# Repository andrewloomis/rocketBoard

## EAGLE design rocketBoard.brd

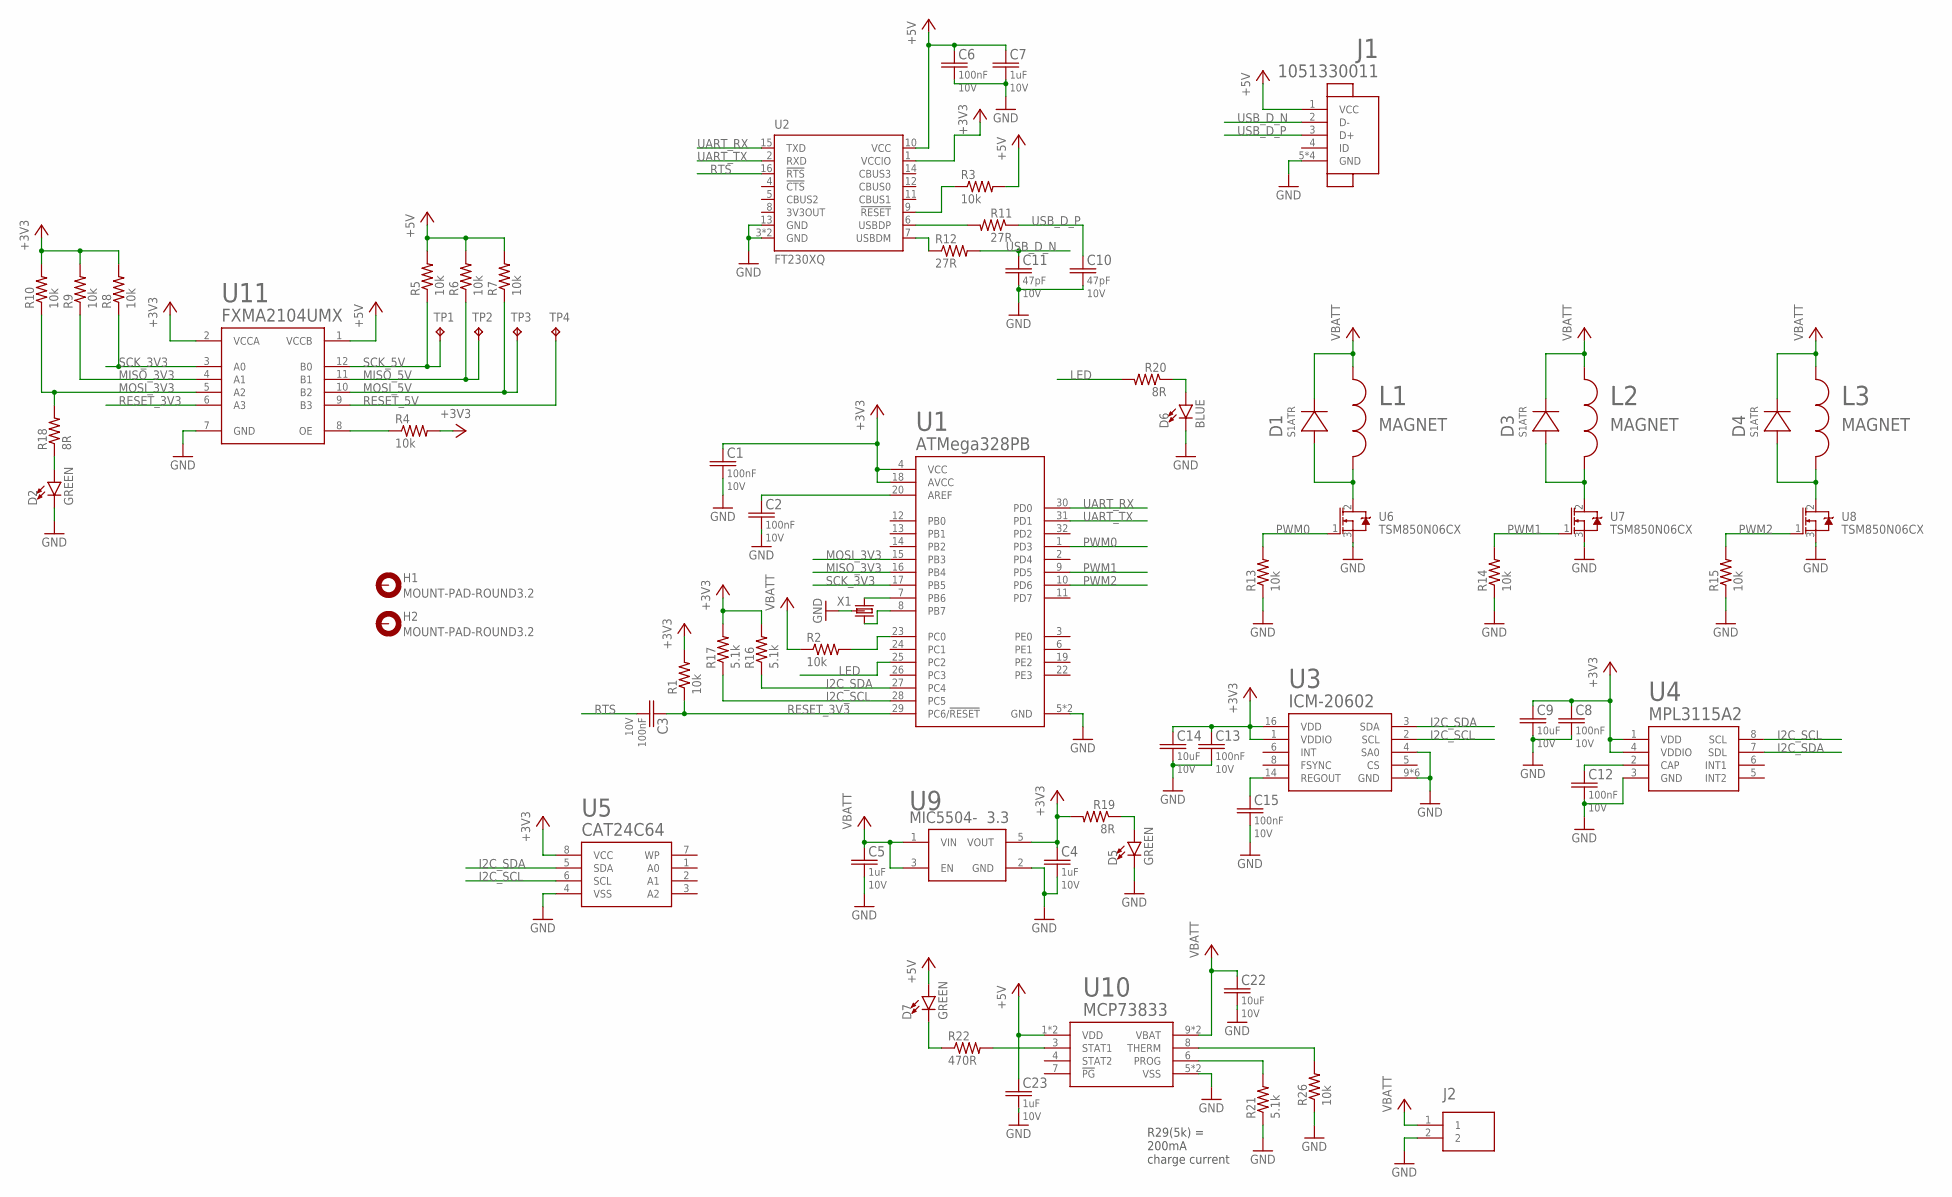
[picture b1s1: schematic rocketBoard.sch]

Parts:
C1, C2, C3, C6, C8, C12, C13, C15: 100nF; C0402
C4, C5, C7, C23: 1uF; C0402
C9, C14, C22: 10uF; C0603
C10, C11: 47pF; C0402
D1, D3, D4: S1ATRSMA; SODFL5226X295
D2, D5, D7: GREEN; LED-0603
D6: BLUE; LED-0603
H1, H2: MOUNT-PAD-ROUND3.2; 3,2-PAD
J1: 1051330011
J2: 2_PIN_CONNECTOR; XH_CONNECTOR
L1, L2, L3: MAGNET
R1, R2, R3, R4, R5, R6, R7, R8, R9, R10, R13, R14, R15, R26: 10k; R0402
R11, R12: 27R; R0402
R16, R17, R21: 5.1k; R0402
R18, R19, R20: 8R; R0402
R22: 470R; R0402
TP1, TP2, TP3, TP4: TPTP20R; TP20R
U1: ATMEGA328PBVQFN; QFN50P500X500X90-32
U2: FT230XQ; QFN16
U3: ICM-20602; LGA16
U4: MPL3115A2; LGA8
U5: CAT24C64SOIC8; SOIC127P600X175-8
U6, U7, U8: TSM850N06CX; SOT95P280X110-3
U9: 3.3; SOT23-5
U10: MCP73833; DFN10-3X3
U11: FXMA2104UMX; 12MLP
X1: CSTCE8M00G55; 3-SMD

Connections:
+3V3: C1.1, C4.1, C8.1, C9.1, C13.1, C14.1, R1.2, R4.2, R8.2, R9.2, R10.2, R16.2, R17.2, R19.2, U1.4 (VCC), U1.18 (AVCC), U2.1 (VCCIO), U3.1 (VDDIO), U3.16 (VDD), U4.1 (VDD), U4.4 (VDDIO), U5.8 (VCC), U9.5 (VOUT), U11.2 (VCCA)
+5V: C6.1, C7.1, C23.1, D7.A, J1.1 (VCC), R3.2, R5.2, R6.2, R7.2, U2.10 (VCC), U10.1 (VDD), U10.2 (VDD), U11.1 (VCCB)
GND: C1.2, C2.2, C4.2, C5.2, C6.2, C7.2, C8.2, C9.2, C10.2, C11.2, C12.2, C13.2, C14.2, C15.2, C22.2, C23.2, D2.C, D5.C, D6.C, J1.5 (GND), J1.P$1 (GND), J1.P$2 (GND), J1.P$3 (GND), J2.2, R13.1, R14.1, R15.1, R21.1, R26.1, U1.5 (GND), U1.21 (GND), U2.3 (GND), U2.13 (GND), U2.TAB (GND), U3.4 (SA0), U3.9 (GND), U3.10 (GND), U3.11 (GND), U3.12 (GND), U3.13 (GND), U3.15 (GND), U4.3 (GND), U5.4 (VSS), U6.3 (S), U7.3 (S), U8.3 (S), U9.2 (GND), U10.5 (VSS), U10.EXP (VSS), U11.7 (GND), X1.2 (GND)
I2C_SCL: R17.1, U1.28 (PC5), U3.2 (SCL), U4.8 (SCL), U5.6 (SCL)
I2C_SDA: R16.1, U1.27 (PC4), U3.3 (SDA), U4.7 (SDL), U5.5 (SDA)
LED: R20.2, U1.25 (PC2)
MISO_3V3: R9.1, U1.16 (PB4), U11.4 (A1)
MISO_5V: R6.1, TP2.TP, U11.11 (B1)
MOSI_3V3: R10.1, R18.2, U1.15 (PB3), U11.5 (A2)
MOSI_5V: R7.1, TP3.TP, U11.10 (B2)
unnamed: R12.1, U2.7 (USBDM)
unnamed: C2.1, U1.20 (AREF)
unnamed: R2.2, U1.23 (PC0)
unnamed: D1.A, L1.-, U6.2 (D)
unnamed: D3.A, L2.-, U7.2 (D)
unnamed: R3.1, U2.9 (!RESET)
unnamed: C12.1, U4.2 (CAP)
unnamed: D4.A, L3.-, U8.2 (D)
unnamed: R11.2, U2.6 (USBDP)
unnamed: U1.8 (PB7), X1.3 (2)
unnamed: U1.7 (PB6), X1.1
unnamed: C15.1, U3.14 (REGOUT)
unnamed: D2.A, R18.1
unnamed: D5.A, R19.1
unnamed: D6.A, R20.1
unnamed: R22.2, U10.3 (STAT1)
unnamed: D7.C, R22.1
unnamed: R26.2, U10.8 (THERM)
unnamed: R21.2, U10.6 (PROG)
unnamed: R4.1, U11.8 (OE)
P$1: C5.1, C22.1, D1.C, D3.C, D4.C, J2.1, L1.+, L2.+, L3.+, R2.1, U9.1 (VIN), U9.3 (EN), U10.9 (VBAT), U10.10 (VBAT)
PWM0: R13.2, U1.1 (PD3), U6.1 (G)
PWM1: R14.2, U1.9 (PD5), U7.1 (G)
PWM2: R15.2, U1.10 (PD6), U8.1 (G)
RESET_3V3: C3.1, R1.1, U1.29 (PC6/!RESET), U11.6 (A3)
RESET_5V: TP4.TP, U11.9 (B3)
RTS: C3.2, U2.16 (!RTS)
SCK_3V3: R8.1, U1.17 (PB5), U11.3 (A0)
SCK_5V: R5.1, TP1.TP, U11.12 (B0)
UART_RX: U1.30 (PD0), U2.15 (TXD)
UART_TX: U1.31 (PD1), U2.2 (RXD)
USB_D_N: C11.1, J1.2 (D-), R12.2
USB_D_P: C10.1, J1.3 (D+), R11.1

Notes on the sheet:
R29(5k) = 200mA charge current

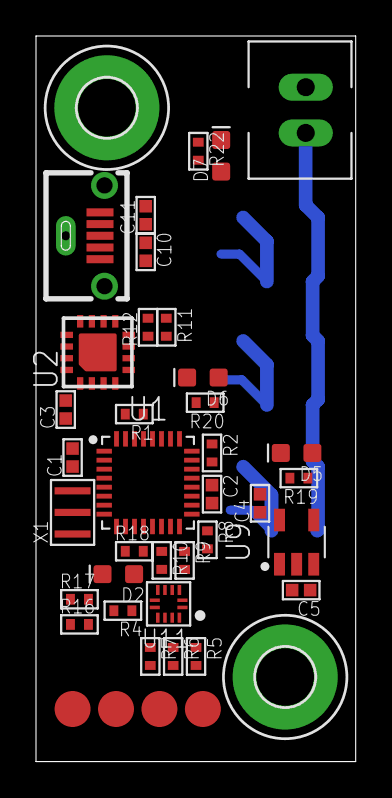
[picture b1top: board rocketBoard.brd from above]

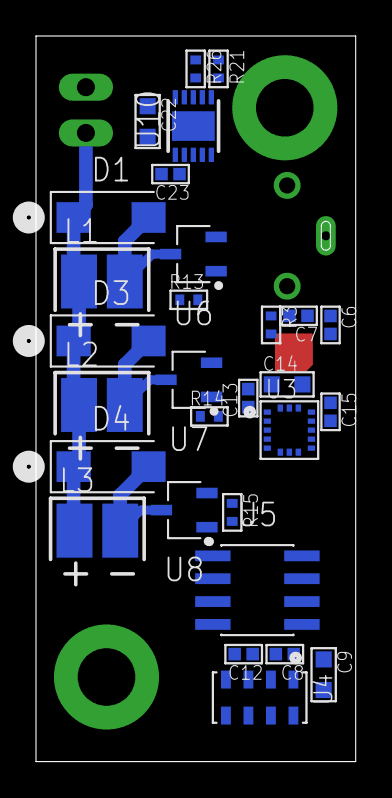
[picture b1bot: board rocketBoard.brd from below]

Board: 2 copper layers, 17.8 x 40.3 mm, 70 parts (29 on the bottom side), 43 nets.

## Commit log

2019-03-16 finished schmatic and initial pcb layout

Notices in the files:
parts and their libraries:
SparkFun-LED: Licensing: Creative Commons ShareAlike 4.0 International - https://creativecommons.org/licenses/by-sa/4.0
